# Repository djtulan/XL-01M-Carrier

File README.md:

# XL-01M-Carrier
This repository includes the KiCAD project for a carrier board for the XL-01M-T and XL-01M-R 2.4GHz audio transmitter.
It is still a work in progress. First PCBs are ordered, but not testet yet.

# Picture of the XL-01M-T and XL-01M-R Modules

# Documents
| Document                                                   |Descripton                                  |
| -----------------------------------------------------------|--------------------------------------------|
| [found docu](/documents/24GNRF24L01XL01MV1.80132905.pdf)   |Found Doku                                  |
| [audio connector](/documents/audio_3.5mm.png)              |3.5mm audio connector used on carrier       |
| [case](/documents/case.png)                                |aluminium case used                         |
| [usb connector](/documents/usb-c.png)                      |USB-C connector for power supply            |

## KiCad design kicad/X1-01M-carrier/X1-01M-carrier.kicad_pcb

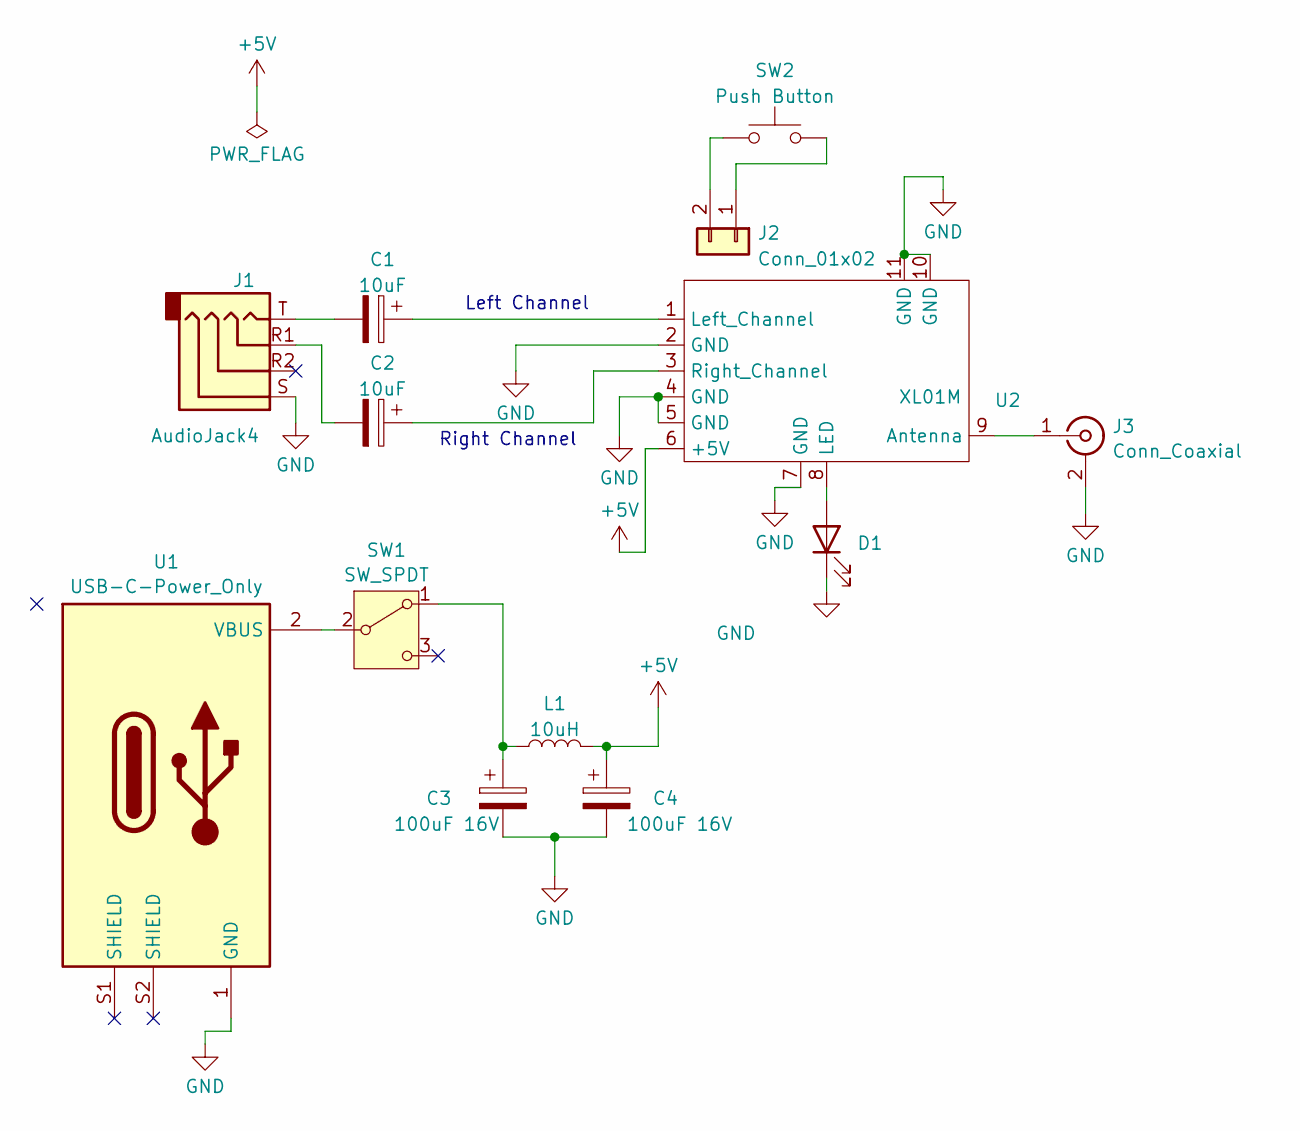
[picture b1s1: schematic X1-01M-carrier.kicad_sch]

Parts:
C1, C2: 10uF; CP_Radial_D5.0mm_P2.50mm
C3, C4: 100uF 16V; CP_Radial_D5.0mm_P2.50mm
D1: LED; LED_D1.8mm_W3.3mm_H2.4mm
J1: AudioJack4; Jack_3.5mm_PJ320E_Horizontal
J2: Conn_01x02; PinSocket_1x02_P2.54mm_Vertical
J3: Conn_Coaxial; SMA_Amphenol_901-143_Horizontal
L1: 10uH; L_Radial_D6.0mm_P4.00mm
SW1: SW_SPDT; SW_Slide_SPDT_Angled_CK_OS102011MA1Q
SW2: Push Button; SW_Tactile_SPST_Angled_PTS645Vx58-2LFS
U1: USB-C-Power_Only; USB_C_Power
U2: XL01M

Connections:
+5V: C4.1, L1.2, U2.6 (+5V)
GND: C3.2, C4.2, D1.1 (K), J1.S, J3.2 (Ext), U1.1 (GND), U2.2 (GND), U2.4 (GND), U2.5 (GND), U2.7 (GND), U2.10 (GND), U2.11 (GND)
unnamed: C1.2, J1.T
unnamed: C2.2, J1.R1
unnamed: D1.2 (A), U2.8 (LED)
unnamed: J2.1, SW2.2
unnamed: J2.2, SW2.1
unnamed: J3.1 (In), U2.9 (Antenna)
unnamed: C3.1, L1.1, SW1.1 (A)
unnamed: SW1.2 (B), U1.2 (VBUS)
unnamed: C1.1, U2.1 (Left_Channel)
unnamed: C2.1, U2.3 (Right_Channel)

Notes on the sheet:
Right Channel
Left Channel

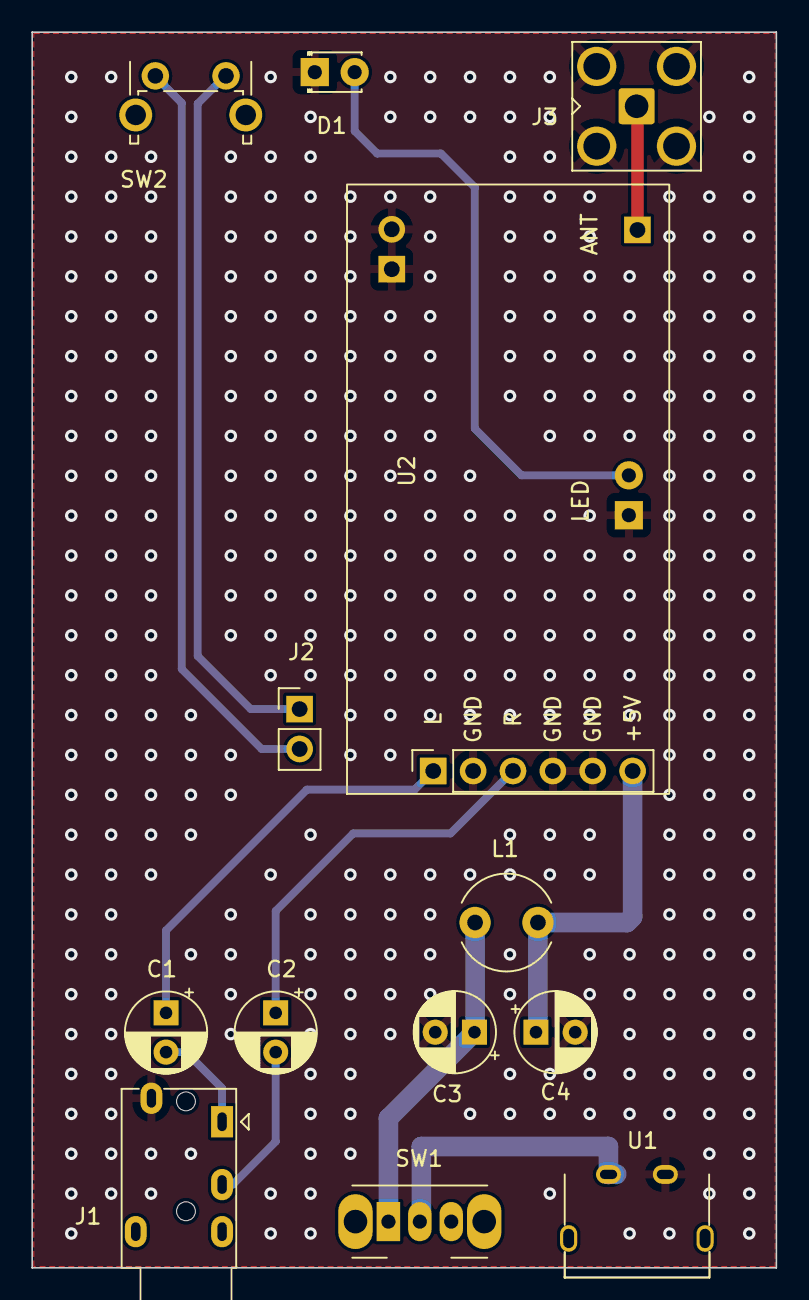
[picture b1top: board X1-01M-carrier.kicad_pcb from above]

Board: 2 copper layers, 47.4 x 78.7 mm, 13 parts (0 on the bottom side), 12 nets.

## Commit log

2024-04-24 added folder
2024-04-24 added kicad
2024-04-24 removed png
2024-05-02 added docs, added gerber, finished layout
2024-05-02 added pics
2024-05-07 added picturer
2024-05-22 added picture
